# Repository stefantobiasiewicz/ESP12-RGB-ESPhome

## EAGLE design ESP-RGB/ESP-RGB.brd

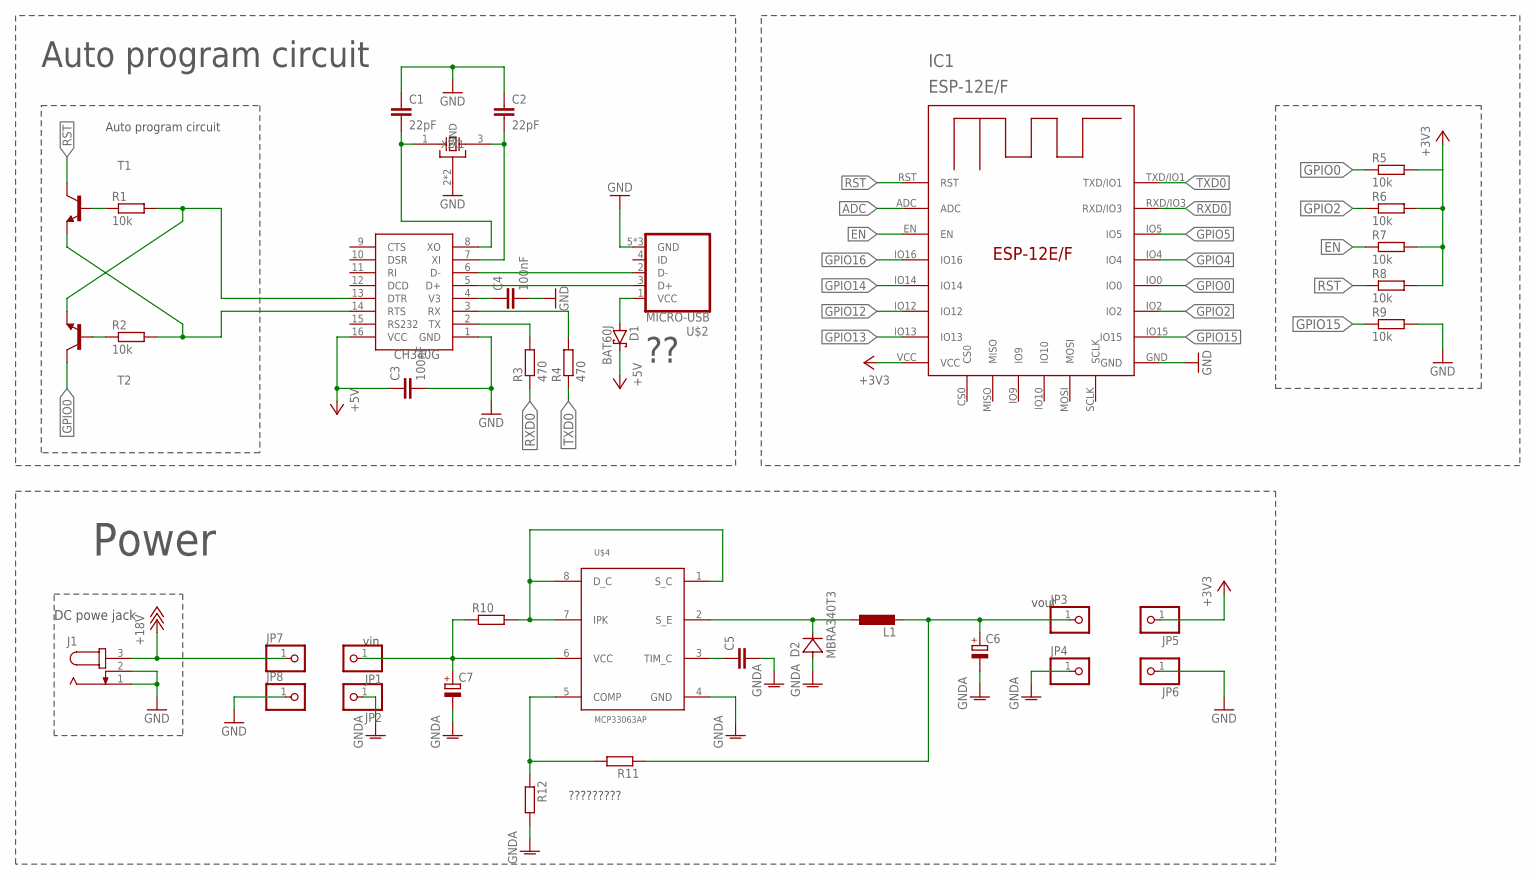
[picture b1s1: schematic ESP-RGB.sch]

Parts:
C1, C2: 22pF; C0805K
C3, C4: 100nF; C0805K
C5: C-EUC0805K; C0805K
C6, C7: CPOL-EU153CLV-0505; 153CLV-0505
D1: BAT60J; SOD323_ST
D2: MBRA340T3; SMA
IC1: ESP-12E/F; ESP-12E
J1: JACK-PLUG0; SPC4077
JP1, JP2, JP3, JP4, JP5, JP6, JP7, JP8: PINHD-1X1; 1X01
L1: L-EUPIS2816; PIS2816
R1, R2, R5, R6, R7, R8, R9: 10k; R0603
R3, R4: 470; R0603
R10: R-EU_R1206W; R1206W
R11, R12: R-EU_R0603; R0603
T1, T2: BC817-16-NPN-SOT23-BEC; SOT23-BEC
U$1: CH340G; SOIC16
U$2: MICRO-USB
U$3: CTS_32X25_SMD; CTS_32X25
U$4: MCP33063AP; DIL08

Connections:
+3V3: IC1.VCC, JP5.1, R5.2, R6.2, R7.2, R8.2
+5V: C3.1, D1.C, U$1.16 (VCC)
+18V: J1.3, JP7.1
ADC: IC1.ADC
EN: IC1.EN, R7.1
GND: C1.1, C2.1, C3.2, C4.2, IC1.GND, J1.1, J1.2, JP6.1, JP8.1, R9.2, U$1.1 (GND), U$2.5 (GND), U$2.GND1 (GND), U$2.GND2 (GND), U$3.2 (GND), U$3.4 (GND)
GNDA: C5.2, C6.-, C7.-, D2.A, JP2.1, JP4.1, R12.2, U$4.4 (GND)
GPIO0: IC1.IO0, R5.1, T2.C
GPIO2: IC1.IO2, R6.1
GPIO4: IC1.IO4
GPIO5: IC1.IO5
GPIO12: IC1.IO12
GPIO13: IC1.IO13
GPIO14: IC1.IO14
GPIO15: IC1.IO15, R9.1
GPIO16: IC1.IO16
unnamed: R2.2, T1.E, U$1.14 (RTS)
unnamed: R1.2, T2.E, U$1.13 (DTR)
unnamed: R1.1, T1.B
unnamed: R2.1, T2.B
unnamed: U$1.6 (D-), U$2.2 (D-)
unnamed: U$1.5 (D+), U$2.3 (D+)
unnamed: D1.A, U$2.1 (VCC)
unnamed: C7.+, JP1.1, R10.1, U$4.6 (VCC)
unnamed: R3.2, U$1.2 (TX)
unnamed: C1.2, U$1.8 (XO), U$3.1 (X1)
unnamed: C2.2, U$1.7 (XI), U$3.3 (X2)
unnamed: R4.2, U$1.3 (RX)
unnamed: C4.1, U$1.4 (V3)
unnamed: R11.2, R12.1, U$4.5 (COMP)
unnamed: R10.2, U$4.1 (S_C), U$4.7 (IPK), U$4.8 (D_C)
unnamed: D2.C, L1.1, U$4.2 (S_E)
unnamed: C5.1, U$4.3 (TIM_C)
unnamed: C6.+, JP3.1, L1.2, R11.1
RST: IC1.RST, R8.1, T1.C
RXD0: IC1.RXD/IO3, R3.1
TXD0: IC1.TXD/IO1, R4.1

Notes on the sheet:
Auto program circuit
DC powe jack
Power
vin
vout
?????????

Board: 2 copper layers, 38 parts (0 on the bottom side), 30 nets, no tracks yet.

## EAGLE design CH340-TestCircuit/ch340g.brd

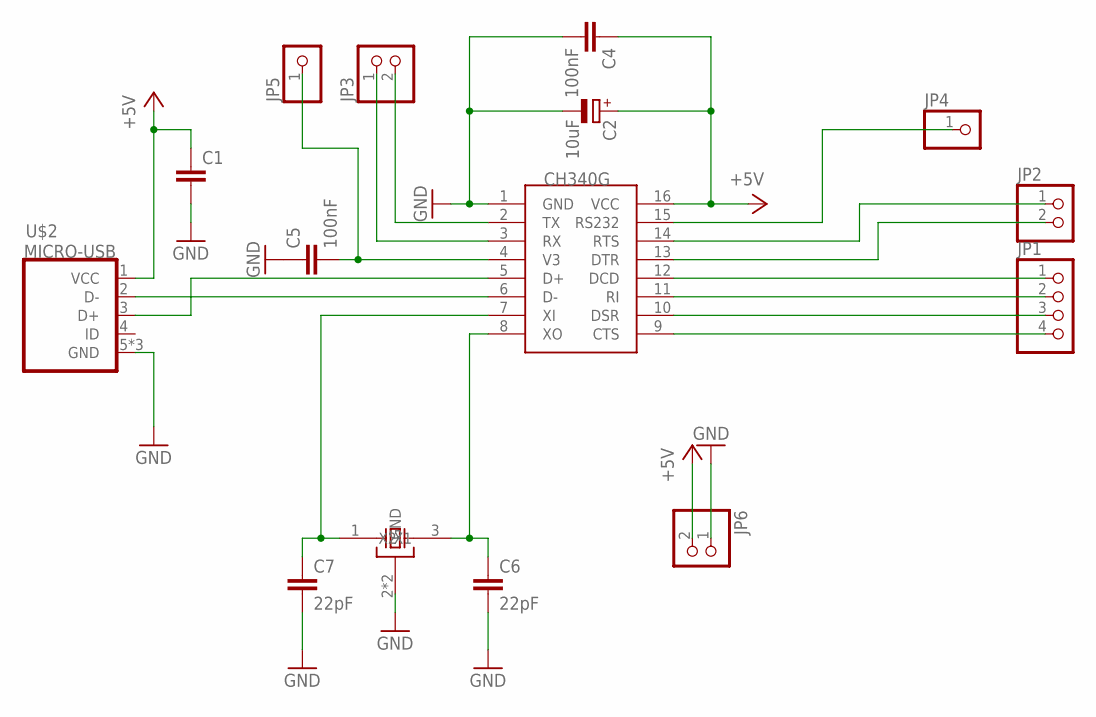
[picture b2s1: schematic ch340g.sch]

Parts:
C1: C-EUC1206K; C1206K
C2: 10uF; SMC_A
C4: 100nF; C0805
C5: 100nF; C1206K
C6, C7: 22pF; C0805
JP1: PINHD-1X4; 1X04
JP2, JP3, JP6: PINHD-1X2; 1X02
JP4, JP5: PINHD-1X1; 1X01
U$1: CH340G; SOIC16
U$2: MICRO-USB
U$3: CTS_32X25_SMD; CTS_32X25

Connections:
+5V: C1.1, C2.+, C4.1, JP6.2, U$1.16 (VCC), U$2.1 (VCC)
GND: C1.2, C2.-, C4.2, C5.1, C6.2, C7.2, JP6.1, U$1.1 (GND), U$2.5 (GND), U$2.GND1 (GND), U$2.GND2 (GND), U$3.2 (GND), U$3.4 (GND)
unnamed: U$1.6 (D-), U$2.2 (D-)
unnamed: U$1.5 (D+), U$2.3 (D+)
unnamed: JP1.1, U$1.12 (DCD)
unnamed: JP1.2, U$1.11 (RI)
unnamed: C7.1, U$1.7 (XI), U$3.1 (X1)
unnamed: C6.1, U$1.8 (XO), U$3.3 (X2)
unnamed: JP2.1, U$1.14 (RTS)
unnamed: JP2.2, U$1.13 (DTR)
unnamed: JP1.3, U$1.10 (DSR)
unnamed: JP1.4, U$1.9 (CTS)
unnamed: JP3.2, U$1.2 (TX)
unnamed: JP3.1, U$1.3 (RX)
unnamed: JP4.1, U$1.15 (RS232)
unnamed: C5.2, JP5.1, U$1.4 (V3)

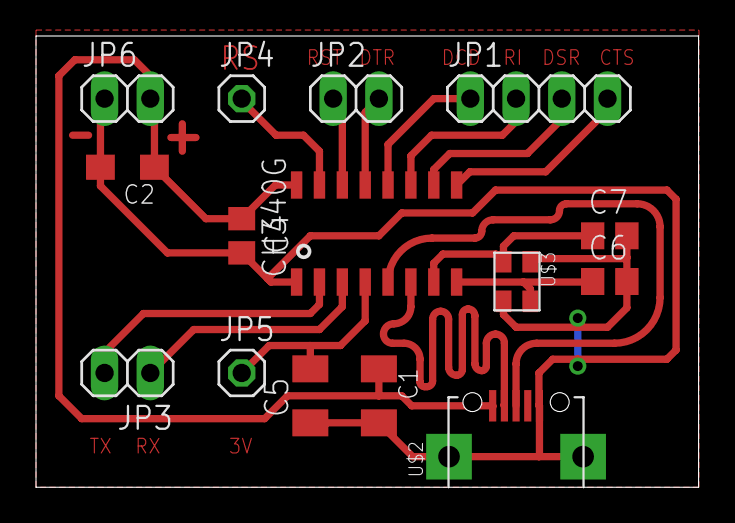
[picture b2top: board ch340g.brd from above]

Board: 2 copper layers, 36.8 x 25.1 mm, 15 parts (0 on the bottom side), 16 nets.

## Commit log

2021-06-12 first setup, ch340 test board
2021-06-13 start
2021-06-13 gitignore
2021-06-13 gitignore m
2021-06-13 gitignore...
2021-06-13 some schematic
2021-06-16 add power module
